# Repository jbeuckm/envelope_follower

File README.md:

# envelope_follower

Envelop follower for eurorack with bonus LFO

Follower: https://www.youtube.com/watch?v=gum4s2Zs2UI

LFO: https://www.davidhaillant.com/wp/wp-content/uploads/lfo-1.5b-20210205.pdf

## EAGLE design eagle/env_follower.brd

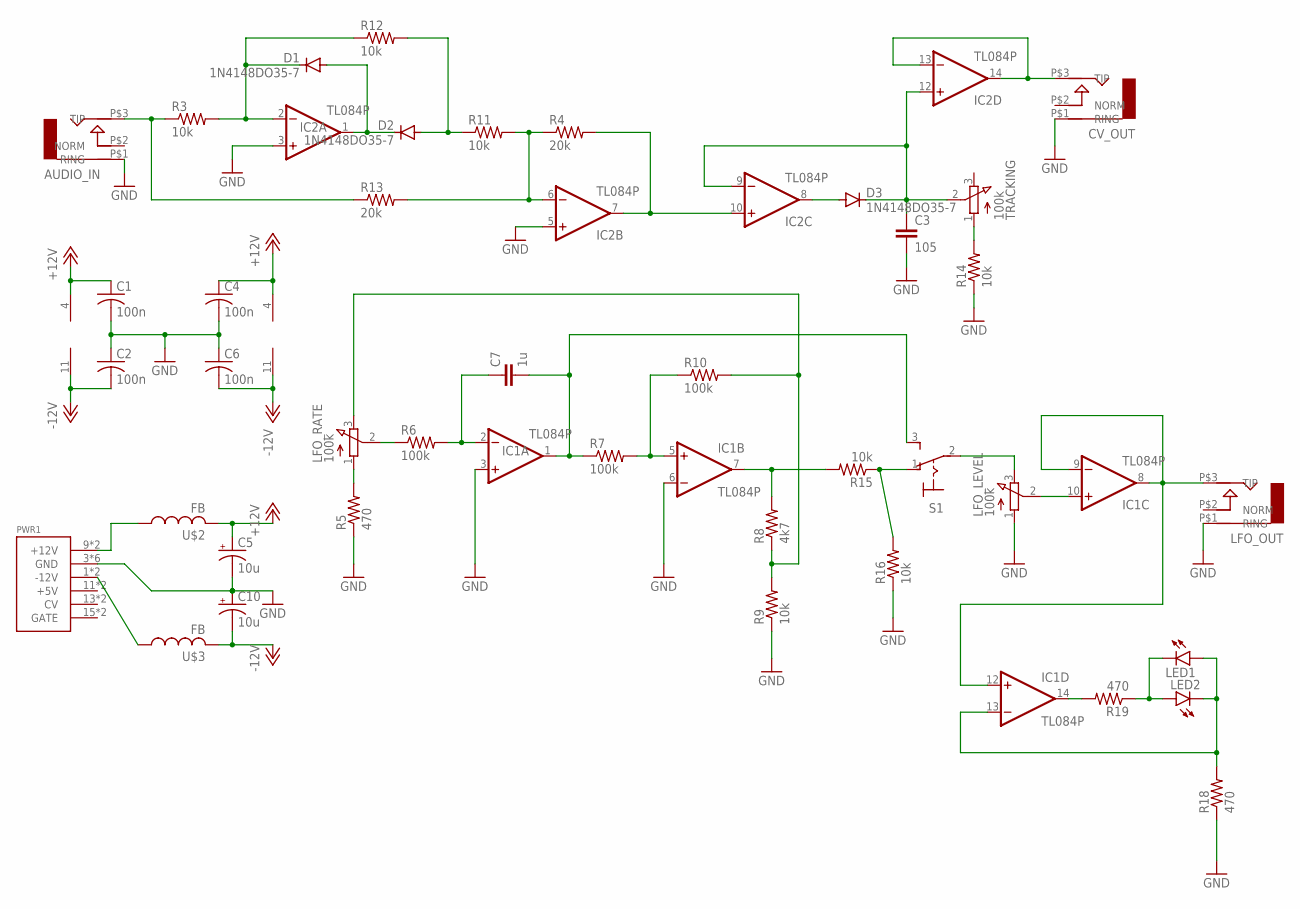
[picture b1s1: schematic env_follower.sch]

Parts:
AUDIO_IN: AUDIO-JACK; ERTHENVAR-JACK-90DEG
C1, C2, C4, C6: 100n; C1206
C3: 105; C7.5B3
C5, C10: 10u; B45181A
C7: 1u; C5B2.5
CV_OUT: AUDIO-JACK; ERTHENVAR-JACK-90DEG
D1, D2, D3: 1N4148DO35-7; DO35-7
IC1, IC2: TL084P; DIL14
LED1, LED2: LED3MM
LFO_LEVEL: 100k; 3RP/1610N
LFO_OUT: AUDIO-JACK; ERTHENVAR-JACK-90DEG
LFO_RATE: 100k; 3RP/1610N
PWR1: POWER; POWER_16
R3, R9, R11, R12, R14, R15, R16: 10k; 0207/7
R4, R13: 20k; 0207/7
R5, R18, R19: 470; 0207/7
R6, R7, R10: 100k; 0207/7
R8: 4k7; 0207/7
S1: M9040P
TRACKING: 100k; 3RP/1610N
U$2, U$3: FB

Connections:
+12V: C1.1, C4.1, C5.+, IC1.4 (V+), IC2.4 (V+), U$2.P$2 (2)
-12V: C2.2, C6.2, C10.-, IC1.11 (V-), IC2.11 (V-), U$3.P$2 (2)
GND: AUDIO_IN.P$1 (RING), C1.2, C2.1, C3.2, C4.2, C5.-, C6.1, C10.+, CV_OUT.P$1 (RING), IC1.3 (+IN), IC1.6 (-IN), IC2.3 (+IN), IC2.5 (+IN), LFO_LEVEL.1 (A), LFO_OUT.P$1 (RING), PWR1.3 (GND), PWR1.4 (GND), PWR1.5 (GND), PWR1.6 (GND), PWR1.7 (GND), PWR1.8 (GND), R5.1, R9.1, R14.1, R16.1, R18.1
unnamed: LFO_RATE.1 (A), R5.2
unnamed: D1.C, IC2.2 (-IN), R3.2, R12.1
unnamed: D1.A, D2.C, IC2.1 (OUT)
unnamed: D2.A, R11.1, R12.2
unnamed: CV_OUT.P$3 (TIP), IC2.13 (-IN), IC2.14 (OUT)
unnamed: LFO_RATE.2 (S), R6.1
unnamed: C7.1, IC1.2 (-IN), R6.2
unnamed: IC2.7 (OUT), IC2.10 (+IN), R4.2
unnamed: AUDIO_IN.P$3 (TIP), R3.1, R13.1
unnamed: C7.2, IC1.1 (OUT), R7.1, S1.3 (S)
unnamed: PWR1.9 (+12V), PWR1.10 (+12V), U$2.P$1 (1)
unnamed: IC1.5 (+IN), R7.2, R10.1
unnamed: IC1.7 (OUT), R8.2, R15.2
unnamed: R15.1, R16.2, S1.1 (O)
unnamed: D3.A, IC2.8 (OUT)
unnamed: LFO_RATE.3 (E), R8.1, R9.2, R10.2
unnamed: PWR1.1 (-12V), PWR1.2 (-12V), U$3.P$1 (1)
unnamed: IC1.8 (OUT), IC1.9 (-IN), IC1.12 (+IN), LFO_OUT.P$3 (TIP)
unnamed: LFO_LEVEL.3 (E), S1.2
unnamed: IC2.6 (-IN), R4.1, R11.2, R13.2
unnamed: C3.1, D3.C, IC2.9 (-IN), IC2.12 (+IN), TRACKING.2 (S)
unnamed: R14.2, TRACKING.1 (A)
unnamed: IC1.10 (+IN), LFO_LEVEL.2 (S)
unnamed: IC1.14 (OUT), R19.2
unnamed: LED1.K (C), LED2.A, R19.1
unnamed: IC1.13 (-IN), LED1.A, LED2.K (C), R18.2

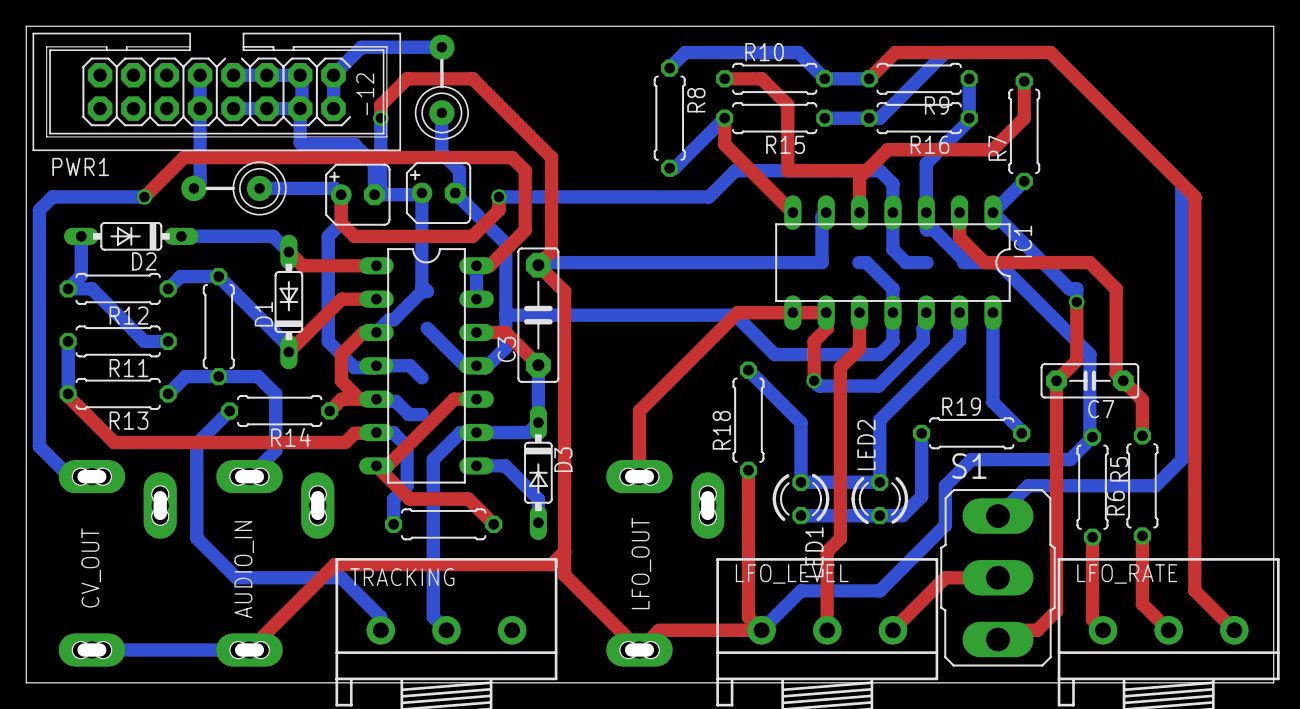
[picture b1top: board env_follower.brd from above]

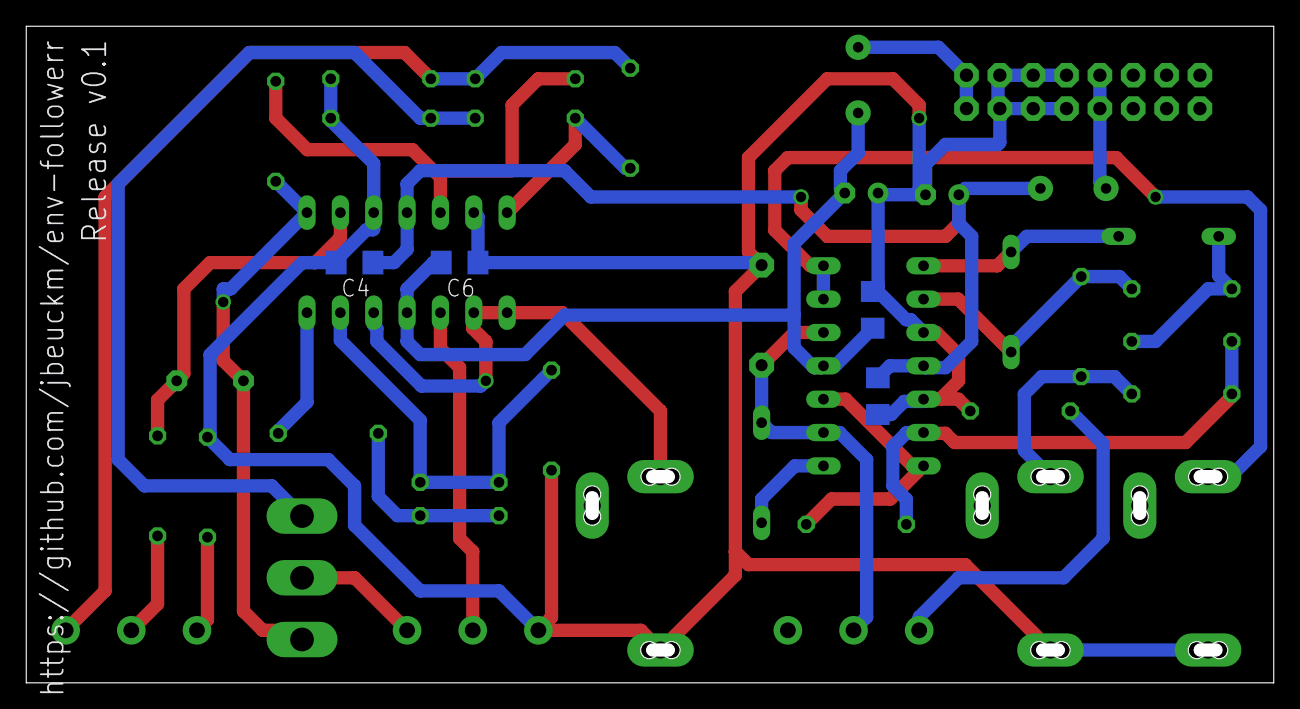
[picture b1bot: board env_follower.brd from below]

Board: 2 copper layers, 94.0 x 49.0 mm, 41 parts (4 on the bottom side), 29 nets.

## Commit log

2021-11-26 follower routed
2021-11-26 routed lfo
2021-11-26 layout tweaks
2021-11-26 board png
2021-11-26 layout into readme
